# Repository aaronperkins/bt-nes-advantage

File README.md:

# Bluetooth NES Advantage

> ⚠️ **This repository is obsolete (v1).** The Bluetooth NES Advantage has been fully redesigned. See the current **v2** repository for the latest hardware, firmware, and docs: **https://github.com/cajunpanda/bluetooth-nes-advantage**

Integrated Bluetooth adapter for the NES Advantage (NES-026)

## Where to buy
Buy a completed kit ready to drop into your NES Advantage here:

[Tindie](https://www.tindie.com/products/cajunpanda/bluetooth-nes-advantage-kit/)

[Ko-Fi](https://ko-fi.com/s/c1f66f6bd5)

## Support
[Discord](https://discord.gg/t8uT8NgTnc)

## Overview
The BT-NES-Advantage is a custom Bluetooth adapter built into the NES Advantage controller, allowing it to connect wirelessly to modern devices as a standard Bluetooth gamepad. This project uses an ESP32-C3 microcontroller to read the NES controller's inputs and transmit them via Bluetooth HID protocol.

## Features
- Wireless Bluetooth LE connectivity
- Turbo and slow motion functions work as normal
- Player select switch
   - Exposes two game input devices for player 1 and 2. The player select switch redirects output to one or the other.
- Standard gamepad HID implementation, tested with:
   - BlueRetro (only works with player 1 switch)
   - Windows
   - Android
   - SteamOS
   - Linux
- *This mod does not work with the 8BitDo Retro Receiver, it doesn't support BLE*
- Long battery life with low power sleep mode
- RGB status LED indication
- Battery level monitoring and reporting
- 5V DC barrel jack charging port

## Usage Instructions

### Pairing the Controller
1. **Turn on the controller** - The controller will automatically wake up when the Start button is held.
2. **Enter pairing mode** - The controller will automatically enter pairing mode when turned on, indicated by a blinking blue LED.
3. **Pair with your device** - On your device (computer, smartphone, game console, etc.), go to Bluetooth settings and select "NES Advantage" from the list of available devices.
4. **Connection successful** - When successfully connected, the blue LED will turn solid.

### Button Mapping
The NES Advantage controller buttons are mapped to standard gamepad controls:
- **D-Pad** - Maps to the directional pad or left analog stick (configurable)
- **A button** - Maps to Button 1 (default profile) or Button 1 (Blue Retro profile)
- **B button** - Maps to Button 2 (default profile) or Button 4 (Blue Retro profile)
- **Start button** - Maps to Start button (Button 12)
- **Select button** - Maps to Select button (Button 11)

#### Button Mapping Profiles
The controller supports multiple button mapping profiles:
1. **Default Profile** - A=Button 1, B=Button 2, Select=Button 11, Start=Button 12
2. **Blue Retro Profile** - A=Button 1, B=Button 4, Select=Button 11, Start=Button 12

To change profiles, hold **A + B + Up** for 5 seconds. The red LED will blink to indicate the current profile (1 blink = Profile 1, 2 blinks = Profile 2).

#### Directional Input Modes
The controller supports three directional input modes:
1. **D-Pad Only** - Directional input sent only to the D-pad/hat switch
2. **Axes Only** - Directional input sent only to the analog stick axes
3. **Both** - Directional input sent to both D-pad and analog stick axes

To change directional modes, hold **Down + A + B** for 5 seconds. The red LED will blink to indicate the current mode (1 blink = D-Pad Only, 2 blinks = Axes Only, 3 blinks = Both).

### Special Functions
- **Sleep mode** - To manually put the controller into sleep mode, hold the **Start button** for 5 seconds. The LEDs will turn off when the controller enters sleep mode.
- **Reconnect/Pair new device** - To disconnect from the current device and enter pairing mode again, hold the **Select button** for 5 seconds.
- **Wake from sleep** - Hold the **Start button** to wake the controller from sleep mode.
- **Change button mapping profile** - Hold **A + B + Up** for 5 seconds to cycle through available button mapping profiles. The red LED will blink to indicate the current profile number.
- **Change directional pad mode** - Hold **Down + A + B** for 5 seconds to cycle through directional input modes (D-Pad Only, Axes Only, Both). The red LED will blink to indicate the current mode.

### LED Indicators
- **Blue LED**:
  - Solid ON - Connected to a device
  - Blinking - In pairing mode (advertising)
  - OFF - Not connected or in sleep mode
- **Green LED**:
  - Blinking - Battery charging
  - Solid ON - Battery fully charged
  - OFF - Not charging
- **Red LED**:
  - Blinking - Low battery (below 20%)
  - OFF - Battery level normal

### Battery and Power
- The controller uses a rechargeable LiPo battery.
- To charge, connect a 5V DC power adapter to the barrel jack.
- Battery level is reported to the connected device when supported.
- The controller will automatically enter sleep mode after 5 minutes of inactivity to conserve power.
- When advertising (pairing mode), the controller will stop advertising after 30 seconds to save battery.

*NES Advantage controller charging via 5V DC barrel jack*

### 3D Printable DC Jack Plug

For a clean installation, a custom 3D printable DC jack plug is available that fits perfectly in the NES Advantage case:

**Download STL file**: [bt_nes_advantage-jack_plug.stl](models/bt_nes_advantage-jack_plug.stl)

Print with a transparent PLA in order to see the status LEDs.

### Troubleshooting
- If unable to pair with a new device, ensure the controller is in pairing mode (blue LED blinking).

## Technical Specifications
- MCU: ESP32-C3 (LOLIN C3 Mini)
- Bluetooth: BLE 5.0
- Battery: 3.7V LiPo 
- Charging: Via 5V DC barrel jack
- Power consumption: ~120mA when connected, <1mA in sleep mode
- Original NES controller compatibility: 100% hardware compatible

## PCB Assembly Instructions

### Bill of Materials (BOM)

| Designator | Qty | Value | Footprint | Description | Notes |
|------------|-----|-------|-----------|-------------|-------|
| C1, C3 | 2 | 10µF | C_0603_1608Metric | Unpolarized capacitor | SMT |
| C2 | 1 | 22µF | C_0603_1608Metric | Unpolarized capacitor | SMT |
| D1, D2, D3 | 3 | 1N5817W | D_SOD-123 | Schottky diode | SMT |
| D4, D5, D6 | 3 | LED | LED_0603_1608Metric | RGB LED (R,G,B) | SMT, 1=K 2=A |
| J1 | 1 | PJ-043-SMT-TR | CUI_PJ-040-SMT-TR | DC Power Jack | SMT, 5V input |
| J2 | 1 | Conn_01x08_Socket | JST_XH_S8B-XH-A_1x08_P2.50mm | 8-pin NES controller connector | Horizontal, THT |
| J3 | 1 | JST Connector | JST_PH_S2B-PH-K_1x02_P2.00mm | LiPo battery connector | Horizontal, THT |
| L1 | 1 | 2.2µH | L_1008_2520Metric | Inductor | SMT |
| R1, R2, R3 | 3 | 200Ω | R_0603_1608Metric | Resistor for LEDs | SMT |
| R7, R8, R9, R10 | 4 | 1KΩ | R_0603_1608Metric | Resistor | SMT |
| R4 | 1 | 2KΩ | R_0603_1608Metric | Resistor | SMT |
| R5, R6 | 2 | 100KΩ | R_0603_1608Metric | Voltage divider for battery monitoring | SMT |
| U1 | 1 | TP4057 | TSOT-23-6 | Li-ion battery charger IC | SMT |
| U2 | 1 | TPS613222ADBV | SOT-23-5 | 5V boost converter | SMT |
| U3 | 1 | ESP32-C3_SUPERMINI_TH | ESP32-C3 SuperMini | ESP32-C3 WiFi/BLE module | THT |

### Parts Sourcing

- **PCB**: [PCBWay Project - Order PCB](https://www.pcbway.com/project/shareproject/Bluetooth_NES_Advantage_865d24ef.html)
- **Parts List**: [Digikey Parts List](https://www.digikey.com/en/mylists/list/EVZPX74W7P)
- **ESP32-C3 SuperMini Module**: [Amazon Link](https://a.co/d/1LoWyFs)
- **J2 Connector Harness Cable**: [Amazon Link](https://a.co/d/abYfjqw)
- **Recommended Battery**: [103450 3.7V LiPo Battery](https://a.co/d/7UFYwX9) (IMPORTANT: Check polarity before connecting)
- **Charging cable**: [DC 2.5x0.7mm Barrel Jack Power Cable](https://a.co/d/4bPUQj2)

### Schematic
[Link to PDF](docs/schematic.pdf)

### Gerber
[Link to Gerber files](pcb/bt-nes-advantage.kicad_pcb.zip)

### Assembly Steps
1. **PCB Preparation**
   - Ensure you have the latest PCB design files from the `pcb` directory
   - Verify that all components from the BOM are available before starting

2. **Component Placement Order**
   - Start with SMD components in this order:
     1. Resistors (R1-R10)
     2. Capacitors (C1-C3)
     3. Diodes (D1-D3)
     4. LEDs (D4-D6) - Note the polarity! Cathode (K) is marked
     5. ICs (U1, U2)
     
*TP4057 U1 pin 1 may not be marked, make sure to get the orientation right by referencing this image and the datasheet.*
     6. Inductor (L1)
     7. DC Jack (J1)
   - Then place through-hole components:
     1. JST connectors (J2, J3)
     2. ESP32-C3 module (U3)

3. **Soldering Guidelines**
   - For SMD components:
     - Use a fine-tip soldering iron (0.5mm or smaller)
     - Recommended temperature: 320-350°C
     - Apply small amount of flux for better results
     - Use tweezers for precise placement
   - For THT components:
     - Secure components flush to PCB before soldering
     - Solder from the lowest-profile components to the highest

4. **Power Connections**
   - The battery connector (J3) is for a 3.7V LiPo battery
     
*Check your battery polarity! There isn't a standard and it may be swapped from what is required!*   
   - Use appropriate JST PH connector with correct polarity
   - The power jack (J1) accepts 5V DC input

5. **Controller Connections**
   - Connect the PCB to the NES Advantage controller using the 8-pin JST XH connector (J2)
   - Pinout from left to right: DATA_P1, LATCH, CLK_P1, DATA_P2, CLK_P2, N/C, +5V, GND
    6. **Pin Mapping**
        - Refer to this pin mapping diagram for connecting the PCB to the NES Advantage controller:

7. **Installation in Controller**
    - Carefully open the NES Advantage controller by removing the screws from the bottom. Refer to this video for a full teardown:

    - Install the battery in the recommended position:

    - Place the PCB in the controller as shown below:

    - Route wires to avoid interference with moving parts of the joystick

    - Finally add some insulating tape to the metal back cover to avoid accidental shorting when reassembling.

## Firmware Instructions

### Option 1: Using Prebuilt Firmware (Recommended)

1. **Download the Firmware**
   - Go to the [Releases page](https://github.com/aaronperkins/bt-nes-advantage/releases) on GitHub
   - Download the latest firmware release

2. **Install ESP Flash Tool**
   - For Linux/Mac: Install `esptool` via pip:
     ```bash
     pip install esptool
     ```
   - For Windows: Download the [ESP Flash Download Tool](https://www.espressif.com/en/support/download/other-tools) from Espressif

3. **Connect the ESP32-C3 SuperMini**
   - Connect the ESP32-C3 SuperMini module to your computer via USB
   - Put the device in download mode by holding the BOOT button while connecting

4. **Flash the Firmware**
   
   #### Option A: Single Merged Binary (Easiest)
   If a merged binary file (`bt_nes_advantage_lolin_c3_mini.bin`) is available:
   ```bash
   esptool.py --chip esp32c3 write_flash 0x0 bt_nes_advantage_lolin_c3_mini.bin
   ```
   
   #### Option B: Individual Binary Files
   If using separate `bootloader.bin`, `partitions.bin`, and `firmware.bin` files:
   - For Linux/Mac (using esptool):
     ```bash
     esptool.py --chip esp32c3 write_flash 0x0000 bootloader.bin 0x8000 partitions.bin 0x10000 firmware.bin
     ```
   - For Windows (using ESP Flash Download Tool):
     - Select Chip Type: ESP32-C3
     - Select bootloader.bin at address 0x0000
     - Select partitions.bin at address 0x8000
     - Select firmware.bin at address 0x10000
     - Select the correct COM port
     - Click "START" to begin flashing

5. **Verify Installation**
   - After flashing completes, press the RST button or disconnect and reconnect the device
   - The blue LED should start blinking indicating pairing mode

### Option 2: Building and Uploading from Source

#### Prerequisites
- VSCode
- PlatformIO VSCode extention
- USB cable for connecting to the ESP32-C3 SuperMini module

#### Building the Firmware with PlatformIO

1. **Install PlatformIO**
   - Install PlatformIO as an extension for VSCode

2. **Clone the Repository**
   ```bash
   git clone https://github.com/aaronperkins/bt-nes-advantage.git
   cd bt-nes-advantage
   ```

3. **Open the Project in PlatformIO**
   - In VSCode with PlatformIO extension, select "Open Project" and choose the `firmware` folder

4. **Configure the Project**
   - The `platformio.ini` file is already configured with the correct settings

5. **Build the Project**
   - In PlatformIO IDE, click on the "Build" button

6. **Connect the ESP32-C3 SuperMini**
   - Connect the ESP32-C3 SuperMini module to your computer via USB
   - If you've already installed it in the controller, you'll need to either:
     - Connect to the USB port on the module

7. **Upload the Firmware**
   - In PlatformIO IDE, click on the "Upload" button

8. **Create Distribution Files (Optional)**
   - If using VS Code with the included tasks, you can create merged firmware files for distribution:
     - Press `Ctrl+Shift+P` and select "Tasks: Run Task"
     - Choose "Full Release Build" to create optimized firmware with merged binary
     - Or choose "Build and Upload Release" to build and upload in one step
     - Distribution files will be created in the `dist/` folder

9. **Monitor Serial Output (Optional)**
   - For debugging, you can monitor the serial output at 115200 baud
   - In PlatformIO IDE, click on the "Serial Monitor" button

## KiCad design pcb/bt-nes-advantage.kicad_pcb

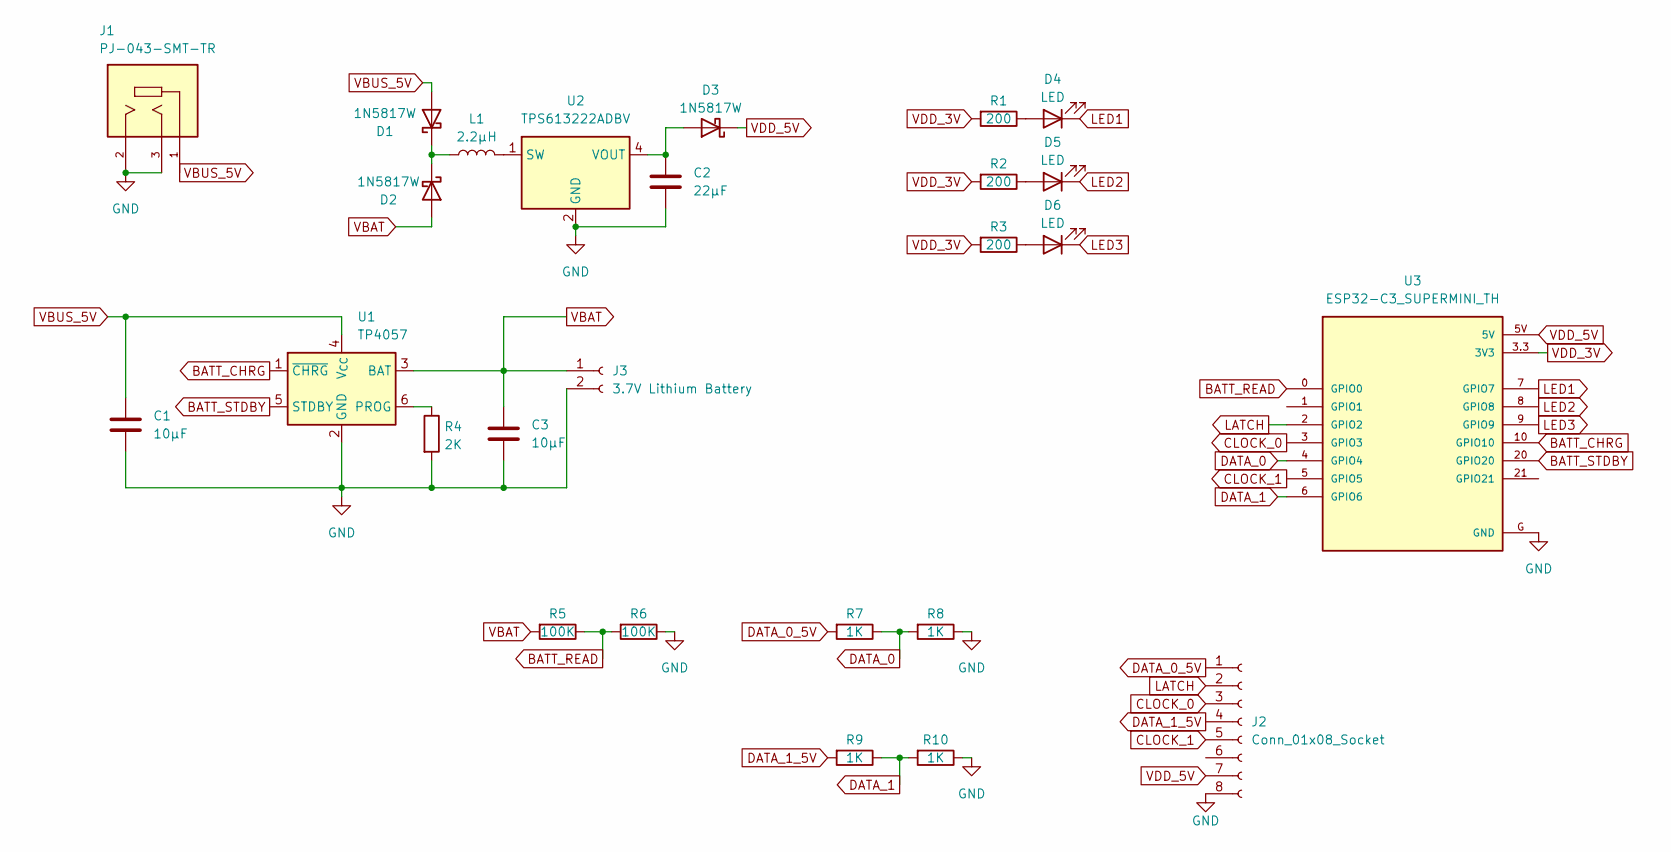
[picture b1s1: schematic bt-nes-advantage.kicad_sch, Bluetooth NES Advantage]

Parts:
C1, C3: 10µF; C_0603_1608Metric_Pad1.08x0.95mm_HandSolder
C2: 22µF; C_0603_1608Metric_Pad1.08x0.95mm_HandSolder
D1, D2, D3: 1N5817W; D_SOD-123
D4, D5, D6: LED; LED_0603_1608Metric_Pad1.05x0.95mm_HandSolder
J1: PJ-043-SMT-TR; CUI_PJ-040-SMT-TR; Mouser Part Number 490-PJ-043-SMT-TR
J2: Conn_01x08_Socket; JST_XH_S8B-XH-A_1x08_P2.50mm_Horizontal
J3: 3.7V Lithium Battery; JST_PH_S2B-PH-K_1x02_P2.00mm_Horizontal
L1: 2.2µH; L_1008_2520Metric_Pad1.43x2.20mm_HandSolder
R1, R2, R3: 200; R_0603_1608Metric_Pad0.98x0.95mm_HandSolder
R4: 2K; R_0603_1608Metric_Pad0.98x0.95mm_HandSolder
R5, R6: 100K; R_0603_1608Metric_Pad0.98x0.95mm_HandSolder
R7, R8, R9, R10: 1K; R_0603_1608Metric_Pad0.98x0.95mm_HandSolder
U1: TP4057; TSOT-23-6
U2: TPS613222ADBV; SOT-23-5
U3: ESP32-C3_SUPERMINI_TH; MODULE_ESP32-C3_SUPERMINI

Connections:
BATT_CHRG: U1.1 (~CHRG), U3.10 (GPIO10)
BATT_READ: R5.1, R6.2, U3.0 (GPIO0)
BATT_STDBY: U1.5 (STDBY), U3.20 (GPIO20)
CLOCK_0: J2.3, U3.3 (GPIO3)
CLOCK_1: J2.5, U3.5 (GPIO5)
DATA_0: R7.1, R8.2, U3.4 (GPIO4)
DATA_0_5V: J2.1, R7.2
DATA_1: R9.1, R10.2, U3.6 (GPIO6)
DATA_1_5V: J2.4, R9.2
GND: C1.2, C2.2, C3.2, J1.2, J1.3, J2.8, J3.2, R4.2, R6.1, R8.1, R10.1, U1.2 (GND), U2.2 (GND), U3.G (GND)
LATCH: J2.2, U3.2 (GPIO2)
LED1: D4.1 (K), U3.7 (GPIO7)
LED2: D5.1 (K), U3.8 (GPIO8)
LED3: D6.1 (K), U3.9 (GPIO9)
unnamed: D1.1 (K), D2.1 (K), L1.1
unnamed: C2.1, D3.2 (A), U2.4 (VOUT)
unnamed: D4.2 (A), R1.1
unnamed: D5.2 (A), R2.1
unnamed: D6.2 (A), R3.1
unnamed: R4.1, U1.6 (PROG)
unnamed: L1.2, U2.1 (SW)
VBAT: C3.1, D2.2 (A), J3.1, R5.2, U1.3 (BAT)
VBUS_5V: C1.1, D1.2 (A), J1.1, U1.4 (V_{CC})
VDD_3V: R1.2, R2.2, R3.2, U3.3.3 (3V3)
VDD_5V: D3.1 (K), J2.7, U3.5V

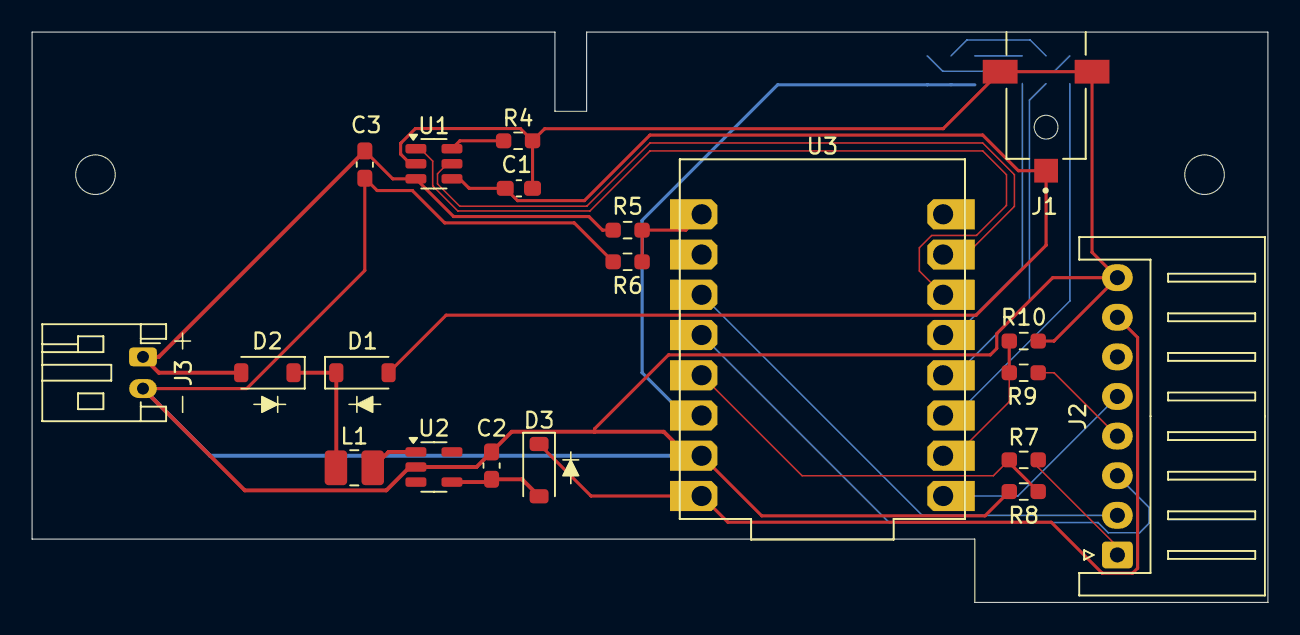
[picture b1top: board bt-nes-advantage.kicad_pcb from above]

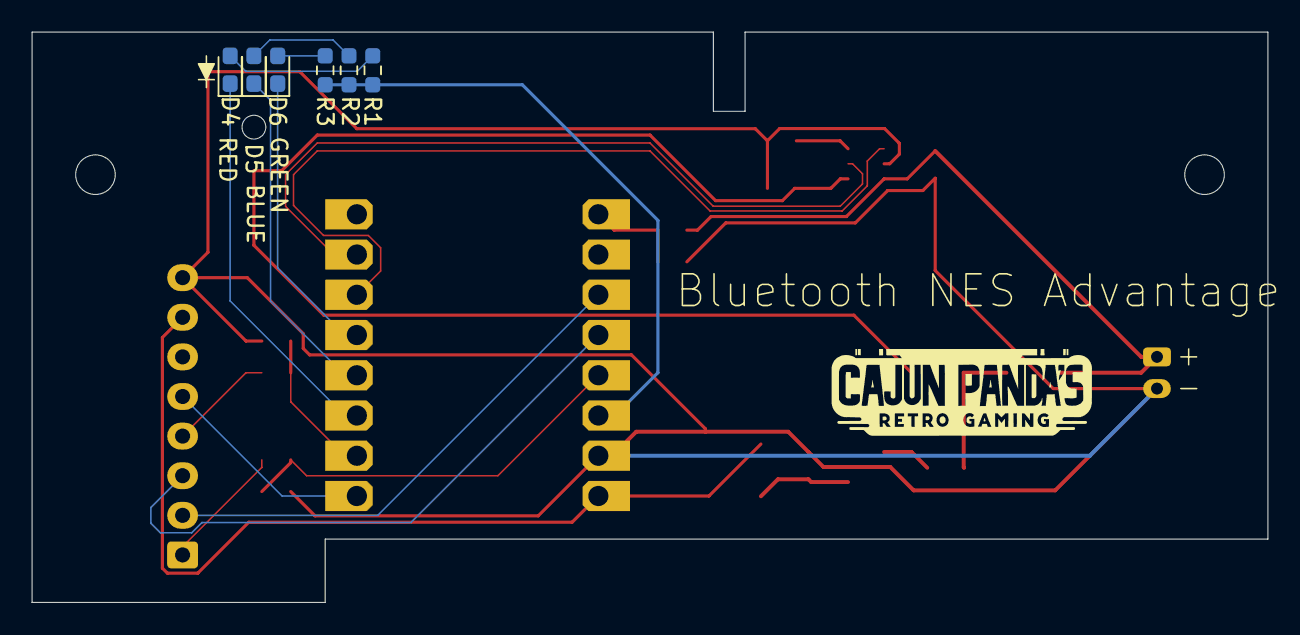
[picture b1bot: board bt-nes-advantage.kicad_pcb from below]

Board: 2 copper layers, 78.0 x 36.0 mm, 26 parts (6 on the bottom side), 25 nets.

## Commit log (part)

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2025-04-23 Added early version of firmware. pcb, and model
2025-04-23 Added .vscode folder
2025-05-12 Converted project to cpp from micropython.
2025-05-12 Added hold start to power off and select to disconnect features.
2025-05-12 Cleanup unused folder.
2025-05-23 New PCB revision. Updated firmware logic.
2025-06-12 pcb update
2025-06-13 Refactor battery management and LED indicators; implement sleep mode functionality
2025-06-15 Refactor code structure for improved readability and maintainability
2025-06-15 Add hero shot image to README for enhanced visual appeal
2025-06-15 Add PCB sourcing link to README for parts procurement
2025-06-15 Update project title in README for consistency
2025-06-15 Update pairing instructions for clarity on controller activation
2025-06-15 Update J2 Connector Harness Cable link in parts list
2025-06-15 Note about back cover.
2025-06-15 Added custopm font used on PCB and PCB images
2025-06-15 Refactor project structure and add BLEJoystick functionality
    - Removed obsolete README file from src/test directory.
    - Added .gitignore file to firmware directory to exclude build artifacts.
    - Created VSCode configuration files (.vscode/extensions.json and .vscode/settings.json) for development environment setup.
    - Implemented BLEJoystick class in firmware/include/BLEJoystick.h and firmware/src/BLEJoystick.cpp for Bluetooth HID joystick functionality.
    - Added main application logic in firmware/src/main.cpp to handle NES controller input and manage BLE connections.
    - Introduced README files in firmware/include and firmware/lib directories to document header files and library usage.
2025-06-15 Remove Adafruit GFX Library from installation instructions
2025-06-15 Removed unused file.
2025-06-18 Add Turbo and slow motion functions to features list in README
2025-06-21 Add NESController class for handling NES controller input
    - Implemented NESController class with methods for reading button states, checking state changes, and managing player selection.
    - Added support for two players with separate button states and selection callbacks.
    - Included methods to retrieve button states, axis values, and hat direction.
    - Initialized controller pins and set up input handling in the constructor and begin method.
    - Implemented debouncing for player selection changes.
2025-06-21 Update pin mapping image to reflect recent changes
2025-06-21 Update pin mapping SVG attachment
2025-06-21 Add video link for NES Advantage teardown in installation instructions
2025-06-22 Add battery state management and reset functionality to NESController
2025-06-24 Update README with firmware installation instructions and usage details
2025-06-27 Fixed bug where controller owuld go to sleep after fully charged even when still plugged in.
2025-06-27 Added gerber link
2025-06-27 Update firmware flashing instructions in README
2025-07-13 Added silkscreen labels for the LED indicators.
2025-07-13 Update firmware download instructions in README to include bootloader and partitions files
2025-07-13 Update PCB design file for BT NES Advantage
2025-07-17 Add button profile mapping feature. Added dpad mode feature. Updated pcb silkscreen to help with assembly. Updated README with assembly tips.
2025-07-22 Enhance BLEJoystick to support multiple players with dynamic input handling and update NESController for player selection
2025-07-23 Updated PCB shape to clear the back panel wedge on some versions of the NES Advantage,
2025-10-13 Update .gitignore and add tasks.json for build and upload processes
2025-10-13 Added missing ground trace for battery voltage detection.
2025-10-13 Updated board revision.
2025-10-13 Update README and tasks.json for clarity and improved instructions
